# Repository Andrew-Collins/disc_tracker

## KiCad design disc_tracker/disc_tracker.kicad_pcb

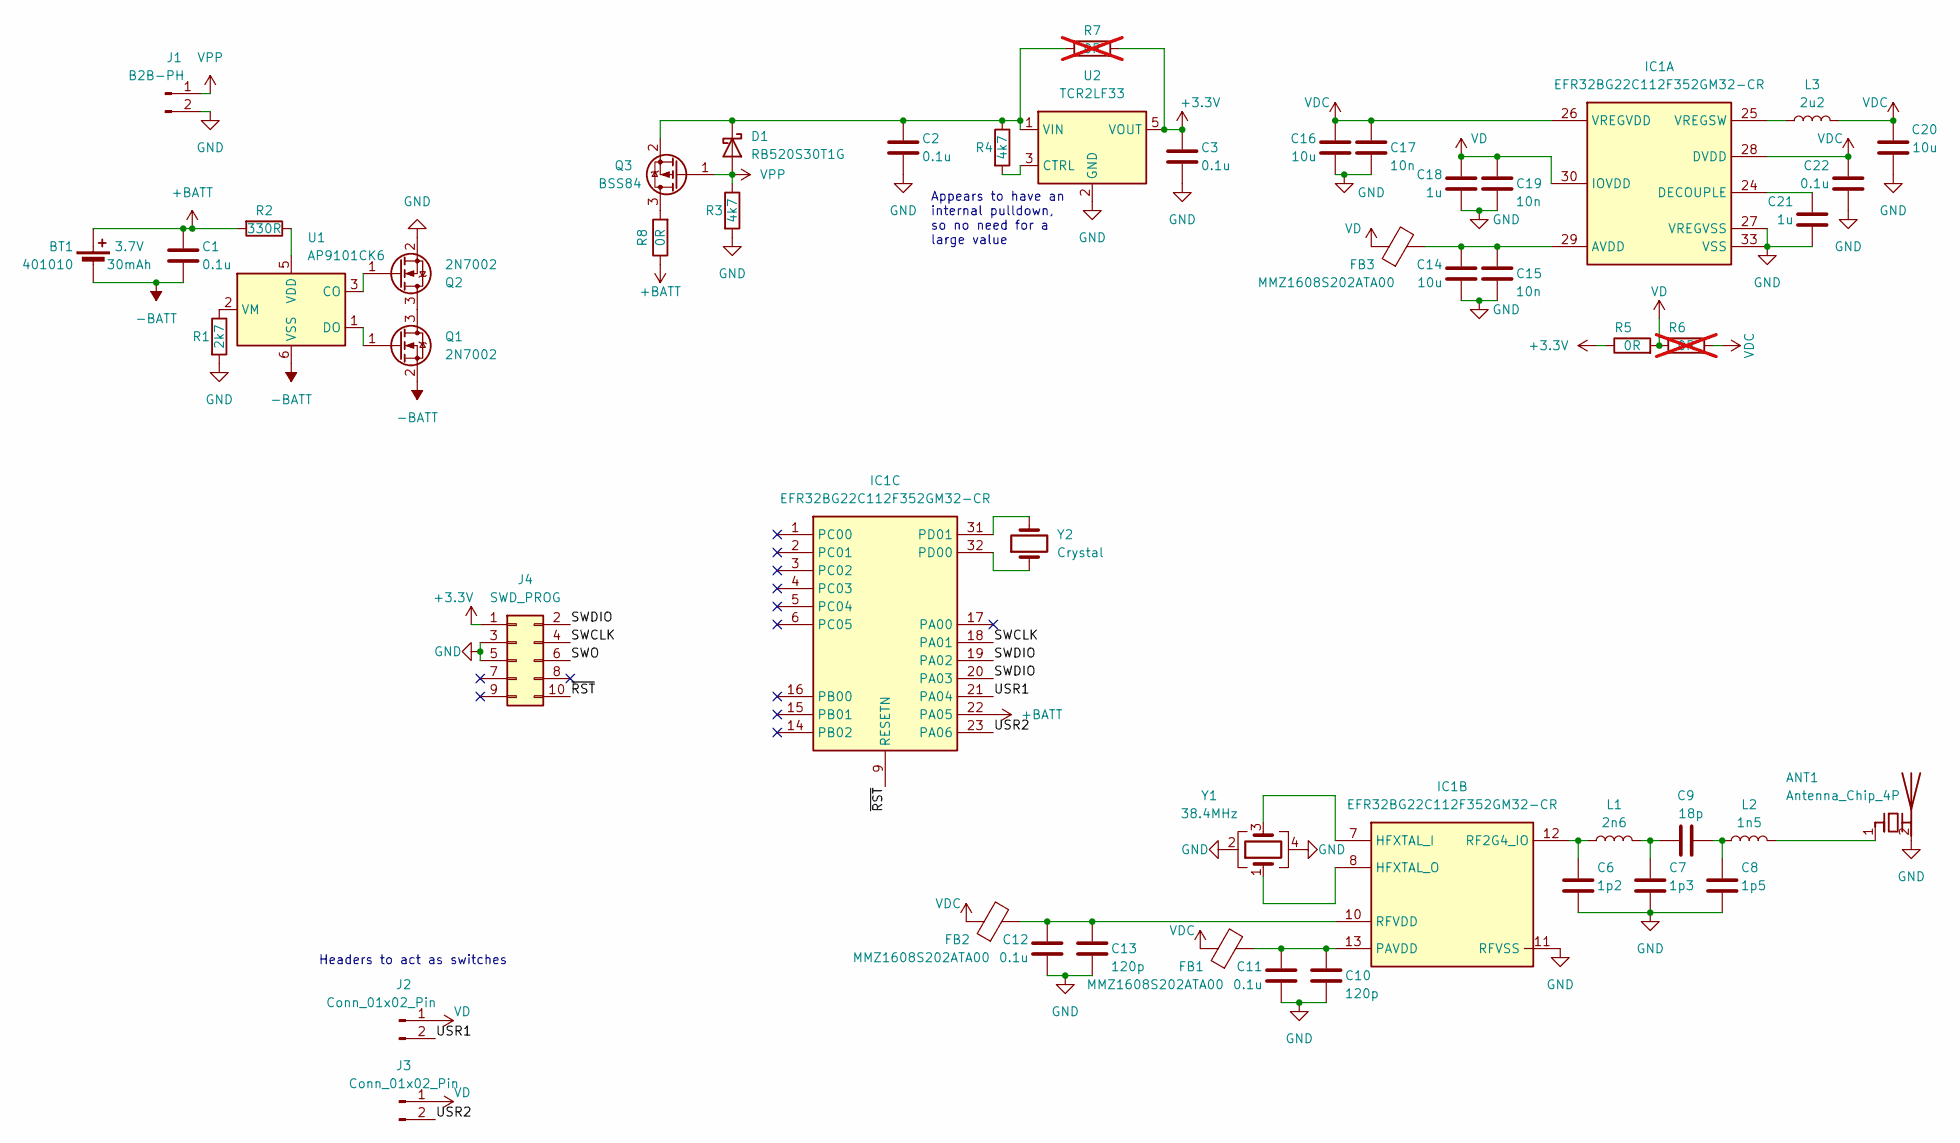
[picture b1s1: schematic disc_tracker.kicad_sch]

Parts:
ANT1: Antenna_Chip_4P; 2450AT18D0100E
BT1: 401010
C1, C2, C3, C11, C12, C22: 0.1u; C_0402_1005Metric
C6: 1p2; C_0402_1005Metric
C7: 1p3; C_0402_1005Metric
C8: 1p5; C_0402_1005Metric
C9: 18p; C_0402_1005Metric
C10, C13: 120p; C_0402_1005Metric
C14, C16, C20: 10u; C_0603_1608Metric
C15, C17, C19: 10n; C_0402_1005Metric
C18, C21: 1u; C_0603_1608Metric
D1: RB520S30T1G; D_SOD-523; mpn RB520S30T1G
FB1, FB2, FB3: MMZ1608S202ATA00; L_0603_1608Metric; mpn MMZ1608S202ATA00
IC1: EFR32BG22C112F352GM32-CR; QFN-32-1EP_4x4mm_P0.4mm_EP2.8x2.8mm; Mouser Part Number 634-ER32BG22112352CR
J1: B2B-PH; JST_PH_B2B-PH-K_1x02_P2.00mm_Vertical
J2, J3: Conn_01x02_Pin; PinHeader_1x02_P1.27mm_Vertical
J4: SWD_PROG; PinHeader_2x05_P1.27mm_Vertical
L1: 2n6; L_0402_1005Metric
L2: 1n5; L_0402_1005Metric
L3: 2u2; L_0402_1005Metric; mpn LQM18PN2R2MFRL
Q1, Q2: 2N7002; SOT-23
Q3: BSS84; SOT-23
R1: 2k7; R_0402_1005Metric
R2: 330R; R_0402_1005Metric
R3, R4: 4k7; R_0402_1005Metric
R5, R8: 0R; R_0402_1005Metric
R6, R7: 0R; R_0402_1005Metric; not fitted
U1: AP9101CK6; SOT-23-6
U2: TCR2LF33; SOT-553
Y1: 38.4MHz; Crystal_SMD_2016-4Pin_2.0x1.6mm; mpn ECS-384-10-37B2-CWN-TR
Y2: Crystal; Crystal_SMD_3215-2Pin_3.2x1.5mm; mpn SC32S-7PF20PPM

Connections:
+3.3V: C3.2, J4.1, R5.1, R7.2, U2.5 (VOUT)
+BATT: BT1.1 (+), C1.2, IC1.22 (PA05), R2.2, R8.1
-BATT: BT1.2 (-), C1.1, Q1.2 (S), U1.6 (VSS)
/SWCLK: IC1.18 (PA01), J4.4
/SWDIO: IC1.19 (PA02), IC1.20 (PA03), J4.2
/SWO: J4.6
/USR1: IC1.21 (PA04), J2.2
/USR2: IC1.23 (PA06), J3.2
/~RST: IC1.9 (RESETN), J4.10
GND: ANT1.2 (GND), ANT1.3 (GND), ANT1.4 (GND), C2.1, C3.1, C6.1, C7.1, C8.1, C10.1, C11.1, C12.1, C13.1, C14.1, C15.1, C16.1, C17.1, C18.1, C19.1, C20.1, C21.1, C22.1, IC1.11 (RFVSS), IC1.27 (VREGVSS), IC1.33 (VSS), J1.2, J4.3, J4.5, Q2.2 (S), R1.2, R3.2, U2.2 (GND), Y1.2, Y1.4
unnamed: ANT1.1 (FEED), L2.2
unnamed: C7.2, C9.2, L1.2
unnamed: C8.2, C9.1, L2.1
unnamed: C2.2, D1.1 (K), Q3.2 (S), R4.1, R7.1, U2.1 (VIN)
unnamed: C14.2, C15.2, FB3.2, IC1.29 (AVDD)
unnamed: C21.2, IC1.24 (DECOUPLE)
unnamed: IC1.25 (VREGSW), L3.1
unnamed: IC1.7 (HFXTAL_I), Y1.3
unnamed: IC1.8 (HFXTAL_O), Y1.1
unnamed: C10.2, C11.2, FB1.2, IC1.13 (PAVDD)
unnamed: C6.2, IC1.12 (RF2G4_IO), L1.1
unnamed: C12.2, C13.2, FB2.2, IC1.10 (RFVDD)
unnamed: IC1.32 (PD00), Y2.1
unnamed: IC1.31 (PD01), Y2.2
unnamed: Q1.3 (D), Q2.3 (D)
unnamed: Q1.1 (G), U1.1 (DO)
unnamed: Q2.1 (G), U1.3 (CO)
unnamed: Q3.3 (D), R8.2
unnamed: R2.1, U1.5 (VDD)
unnamed: R1.1, U1.2 (VM)
unnamed: R4.2, U2.3 (CTRL)
VD: C18.2, C19.2, FB3.1, IC1.30 (IOVDD), J2.1, J3.1, R5.2, R6.1
VDC: C16.2, C17.2, C20.2, C22.2, FB1.1, FB2.1, IC1.26 (VREGVDD), IC1.28 (DVDD), L3.2, R6.2
VPP: D1.2 (A), J1.1, Q3.1 (G), R3.1

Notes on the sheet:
Appears to have an internal pulldown, so no need for a large value
Headers to act as switches

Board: 2 copper layers, 48 parts (0 on the bottom side), 33 nets, no tracks yet.

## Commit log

2023-10-22 Most footprints and symbols added
2023-10-22 QFN32 added for Silabs chip. Regulator symbol added. All ICs on schematic
2023-10-22 Schematic should be done. Starting component placment. Will need to go to 0201 for decoupling caps maybe
